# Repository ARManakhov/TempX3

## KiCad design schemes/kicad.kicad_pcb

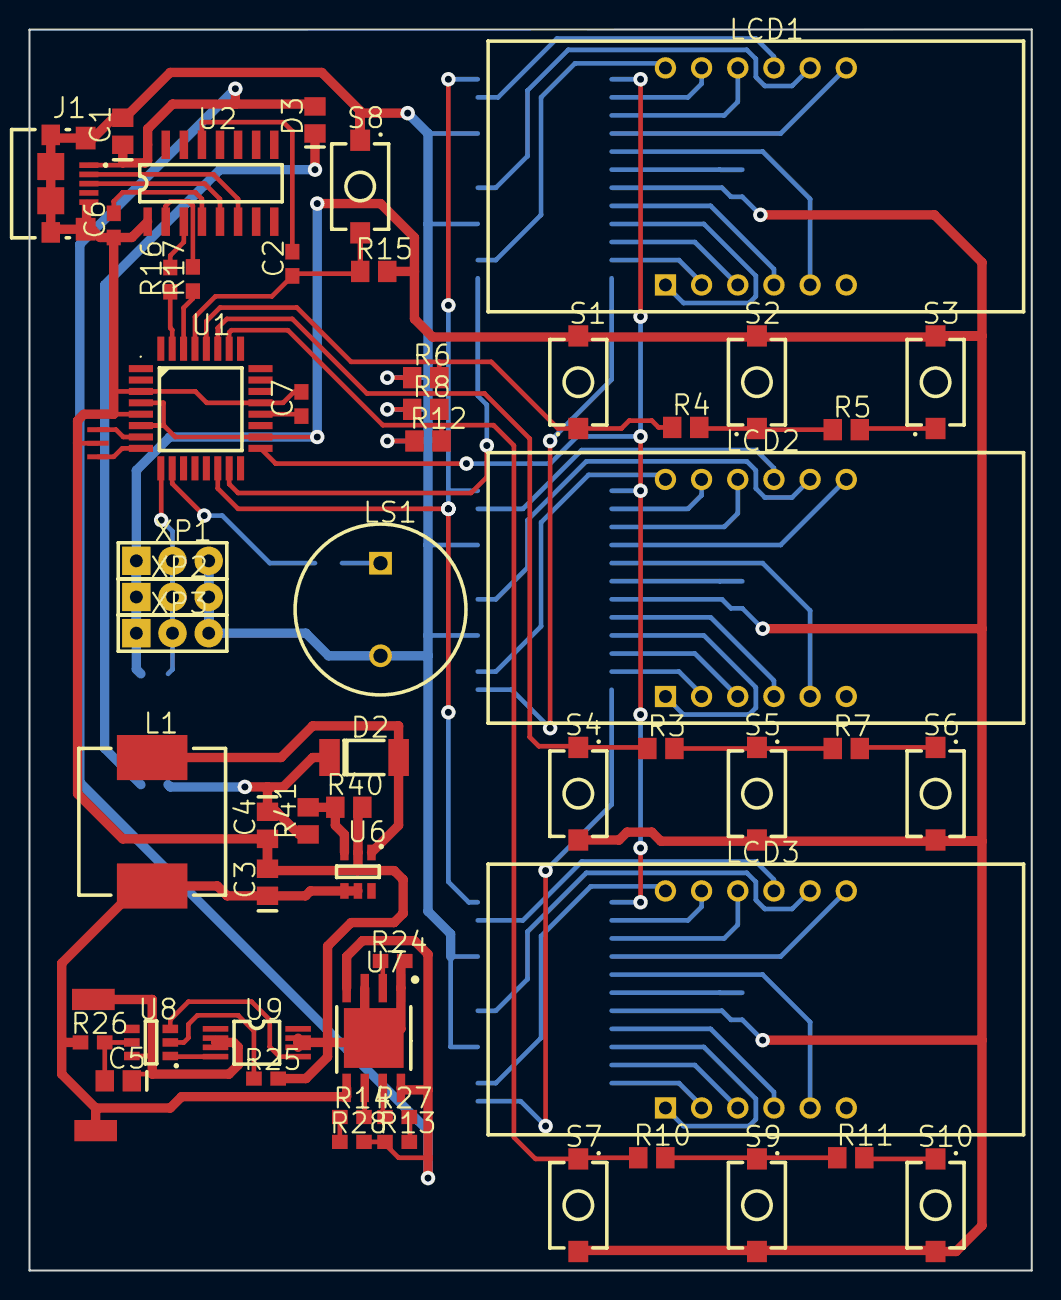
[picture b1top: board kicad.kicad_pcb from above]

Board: 2 copper layers, 70.4 x 87.1 mm, 69 parts (0 on the bottom side), 83 nets.

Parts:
C1, C3: CAP_0805
C2, C6, C7: CAP_0603
C4, C5: CAP_0805; CAP_0805_C4
D1: DIO_0805
D2: DIO_2009
D3: DIO_0805; DIO_0805_D3
J1: 1981568-1
L1: IHLP4040DZER1R0
LCD1, LCD2, LCD3: BC56-12
LS1: AT-1220-TT-R; PB-1220PQ
Pad1, Pad2, Pad3: PAD; RES_0805_Pad1
Pad4, Pad5: PAD; Pad
R1, R2, R9, R34: RES_0805
R3, R4, R5, R6, R7, R8, R10, R11, R12, R15: RES_0805; RES_0805_R4
R13, R16, R24, R25, R28: RES_0603
R14, R17, R26, R27: RES_0603; RES_0603_R14
R40, R41: RES_0805_R4
R42: RES_0805; RES_0805_R42
S1, S2, S3: KSR211GLFS; KSR-G_S1
S4, S5, S6, S7, S8, S9, S10: KSR211GLFS; KSR-G
U1: ATMEGA328_TQFP32; QFP-32_9x9x0.8
U2: SOIC-16/150MIL; SOIC-16_150mil
U3, U4, U5: MAX7219EWG; SOIC-24_300mil
U6: SOT23-6
U7: SOP-8EP/7.8X1.27; SOP-8EP_7.8x1.27
U8: SOT23-6; SOT23-6_U8
U9: TSSOP-8
XP1, XP2, XP3: PLS_3

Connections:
Net_0: Pad1.1, U1.8
Net_1: Pad3.1, U1.7
Net_2: C1.2, C3.2, C4.2, C6.1, C7.2, J1.5, J1.6, J1.7, J1.8, J1.9, J1.10, J1.11, LS1.2, Pad2.1, R6.1, R8.1, R12.1, R24.2, R25.2, R40.2, S8.1, U1.3, U1.5, U1.21, U2.1, U3.4, U3.9, U4.4, U4.9, U5.4, U5.9, U6.2, U7.1, U7.3, U7.9, U9.6, U9.7, XP1.3, XP2.3, XP3.3
Net_3: R16.2, U2.3
Net_4: R17.1, U2.2
Net_5: C1.1, D3.2, J1.1, R13.1, R28.2, U2.16, U7.4, U7.8
Net_6: U1.15, U3.1
Net_7: J1.2, U2.6
Net_8: J1.3, U2.5
Net_9: C2.1, R15.1, S8.2, U1.29
Net_10: C2.2, U2.13
Net_11: U1.14, U3.12, U4.12, U5.12
Net_12: U1.17, U3.13, U4.13, U5.13
Net_13: LCD1.11, U3.14
Net_14: LCD1.10, U3.15
Net_15: LCD1.7, U3.16
Net_16: LCD1.5, U3.17
Net_17: LCD1.4, U3.20
Net_18: LCD1.1, U3.21
Net_19: LCD1.3, U3.22
Net_20: LCD1.2, U3.23
Net_21: R1.2, U3.18
Net_22: U3.24, U4.1
Net_23: LCD1.12, U3.2
Net_24: LCD1.9, U3.11
Net_25: LCD1.8, U3.6
Net_26: U4.24, U5.1
Net_27: LCD2.11, U4.14
Net_28: LCD2.10, U4.15
Net_29: LCD2.7, U4.16
Net_30: LCD2.5, U4.17
Net_31: LCD2.4, U4.20
Net_32: LCD2.1, U4.21
Net_33: LCD2.3, U4.22
Net_34: LCD2.2, U4.23
Net_35: R2.2, U4.18
Net_36: LCD2.12, U4.2
Net_37: LCD2.9, U4.11
Net_38: LCD2.8, U4.6
Net_39: R4.1, R6.2, S1.1, U1.28
Net_40: R4.2, R5.1, S2.1
Net_41: R3.1, S4.1, U1.27
Net_42: R3.2, R7.1, S5.1
Net_43: R7.2, S6.1
Net_44: C4.1, D1.1, D2.1, R41.1
Net_45: C7.1, U1.20
Net_46: LCD3.11, U5.14
Net_47: LCD3.10, U5.15
Net_48: LCD3.7, U5.16
Net_49: LCD3.5, U5.17
Net_50: LCD3.4, U5.20
Net_51: LCD3.1, U5.21
Net_52: LCD3.3, U5.22
Net_53: R5.2, S3.1
Net_54: LCD3.2, U5.23
Net_55: R9.2, U5.18
Net_56: LCD3.12, U5.2
Net_57: LCD3.9, U5.11
Net_58: LCD3.8, U5.6
Net_59: R10.1, R12.2, S7.1, U1.26
Net_60: R10.2, R11.1, S9.1
Net_61: R11.2, S10.1
Net_62: R16.1, U1.31
Net_63: R24.1, U7.2
Net_64: C5.1, Pad4.-, U8.6, U9.2, U9.3
Net_65: U8.1, U9.4
Net_66: R17.2, U1.30
Net_67: R27.2, U7.7
Net_68: R14.1, U7.6
Net_69: LS1.1, R34.2
Net_70: R1.1, R2.1, R9.1, R15.2, R42.2, S1.2, S2.2, S3.2, S4.2, S5.2, S6.2, S7.2, S9.2, S10.2, U1.4, U1.6, U1.18, U3.19, U4.19, U5.19, XP1.1, XP2.1, XP3.1
Net_71: R42.1, U1.9, XP1.2, XP2.2, XP3.2
Net_72: R34.1, U1.10
Net_73: D1.2, D3.1
Net_76: R14.2, R28.1
Net_78: C6.2, U2.4
Net_79: R25.1, U8.2
Net_80: U8.3, U9.5
Net_81: R13.2, R27.1
Net_82: C5.2, R26.1, U8.5
Net_83: C3.1, L1.2, R26.2, U6.4, U6.5, U7.5
Net_85: D2.2, L1.1, U6.1
Net_87: R40.1, R41.2, U6.3

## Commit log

2020-08-15 first commit, almost implemented all functianality
2020-09-03 partialy implemented interface manager
2020-09-03 partialy implemented display manager
2020-09-05 added basic functions to interface
2020-09-05 max min temp save load implemented
2020-09-07 added brightness regulation
2020-09-07 implemented auto sensor detection, and small refactoring
2020-09-07 implemented smart sensors connection managment
2020-09-09 added eeprom save load data about sensors
2020-09-09 eeprom work with sensors implemented, some refactor
2020-09-09 impl sensor auto save to eeprom
2020-09-09 fixing small bug
2020-09-09 fixed eeprom sensors bug
2020-09-11 fix gitignore
2020-09-11 git ignore fix. again
2020-09-24 beeper implemented
2020-09-26 made scheme import to kicad
2020-09-26 gitignore fix
